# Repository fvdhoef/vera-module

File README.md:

# VERA module - Video Embedded Retro Adapter
This repository contains the files related to the VERA module. This module is developed for the Commander X16 computer by The 8-Bit Guy.

**NOTE**: The Commander X16 logo is part of the Commander X16 project and should not be used when the module is used with other projects.

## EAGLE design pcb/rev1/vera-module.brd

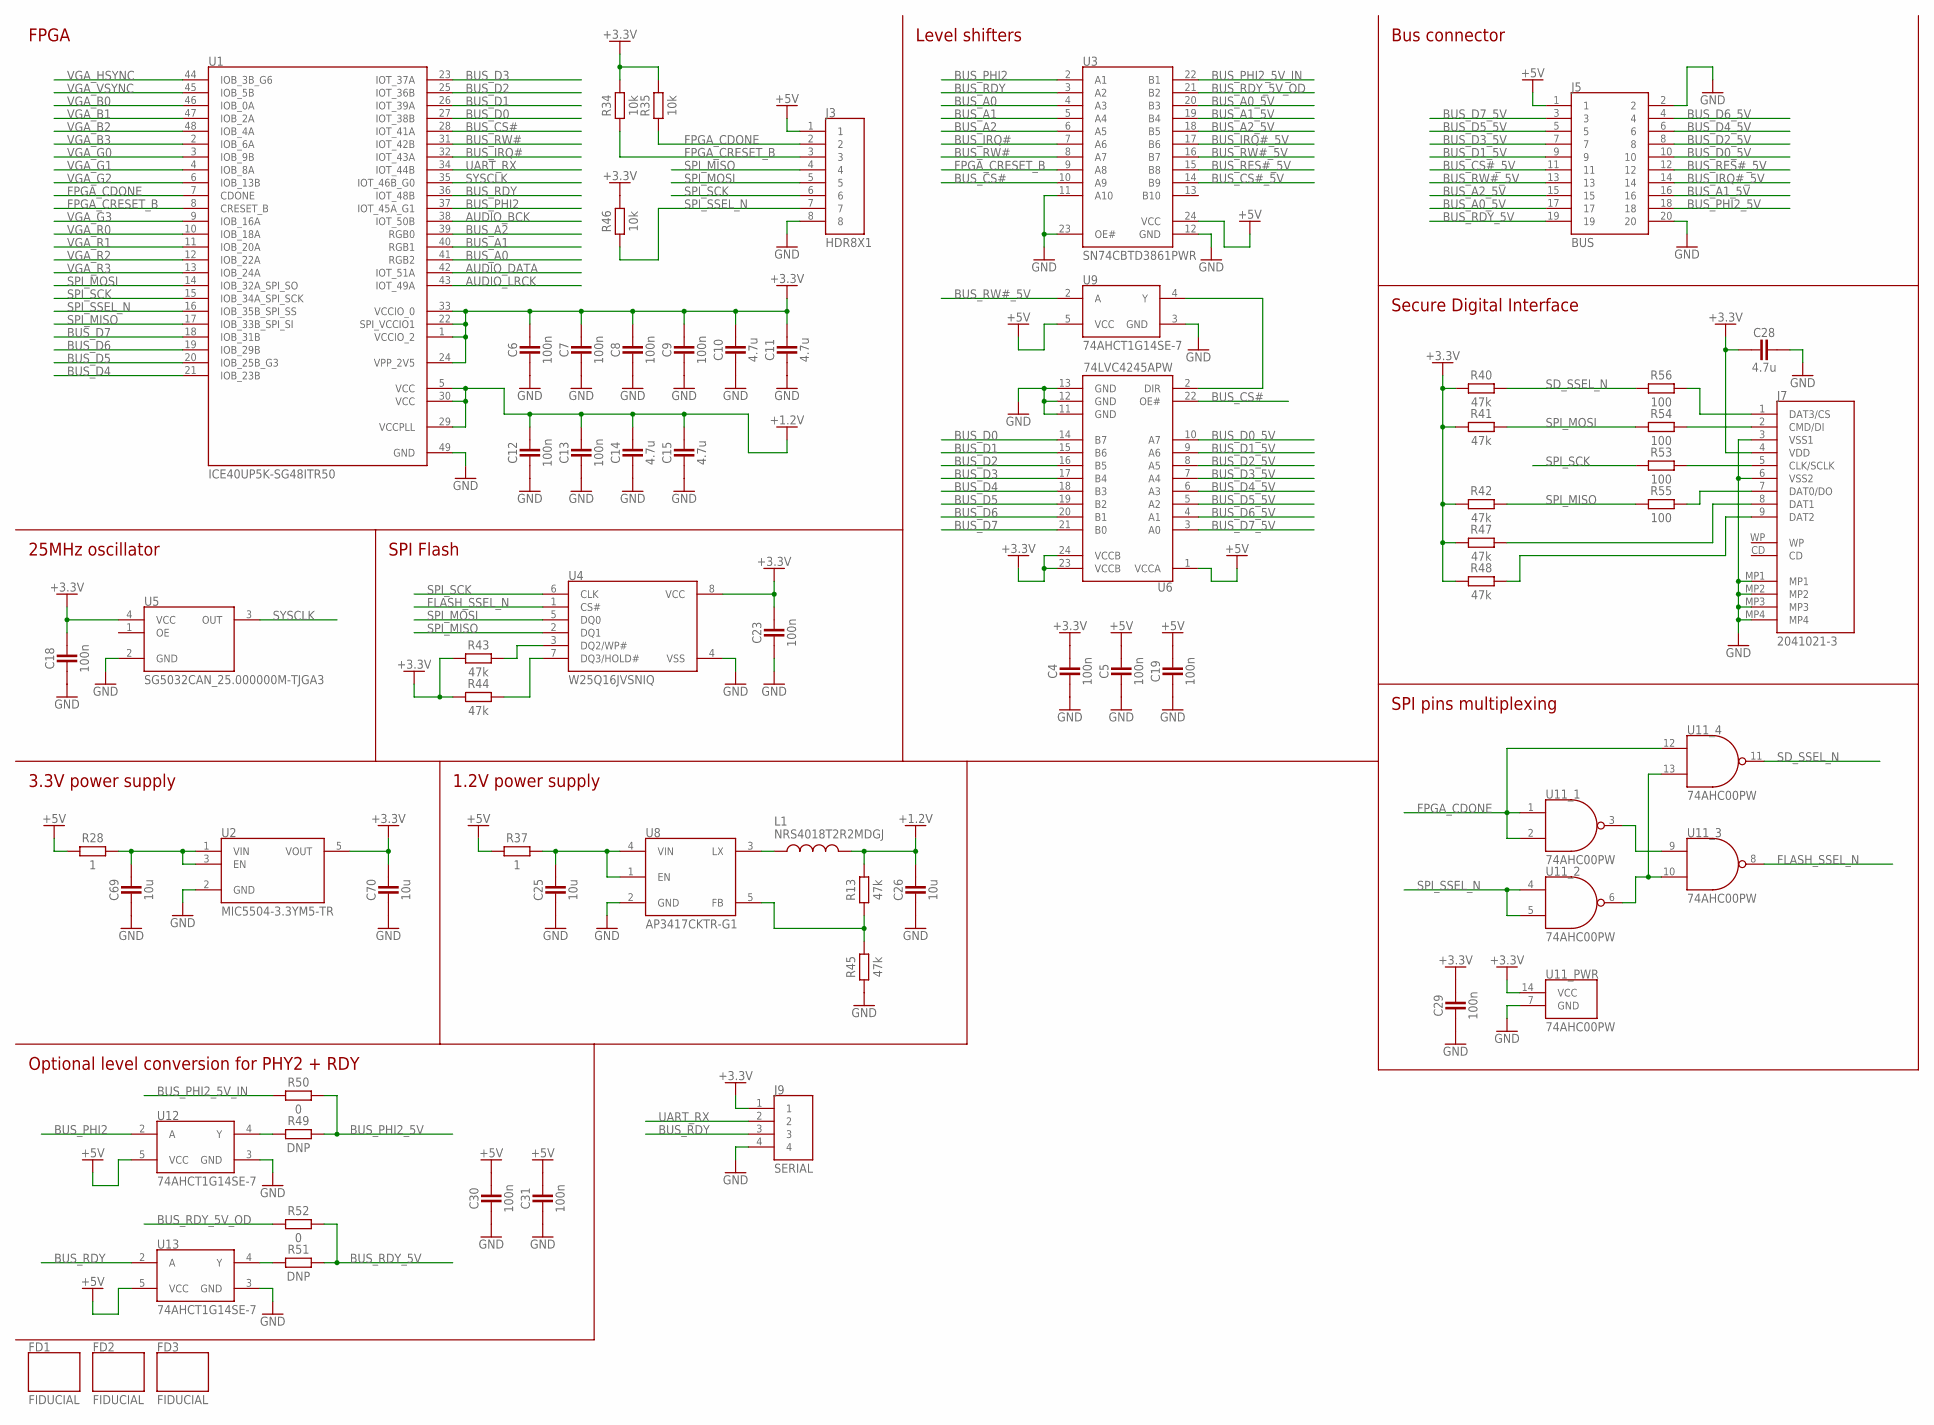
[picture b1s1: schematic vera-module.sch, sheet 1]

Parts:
C4, C5, C6, C7, C8, C9, C12, C13, C18, C19, C23, C29, C30, C31: 100n; C0603
C10, C11, C14, C15, C28: 4.7u; C0603
C25, C26, C69, C70: 10u; C0805
FD1, FD2, FD3: FIDUCIAL
J3: HDR8X1
J5: BUS; HDR2X10
J7: 2041021-3
J9: SERIAL; HDR4X1
L1: NRS4018T2R2MDGJ; NRS4018
R13, R40, R41, R42, R43, R44, R45, R47, R48: 47k; R0603
R28, R37: 1; R0603
R34, R35, R46: 10k; R0603
R49, R51: DNP; R0603
R50, R52: 0; R0603
R53, R54, R55, R56: 100; R0603
U1: ICE40UP5K-SG48ITR50; QFN-48
U2: MIC5504-3.3YM5-TR; SOT-23-5
U3: SN74CBTD3861PWR; TSSOP-24
U4: W25Q16JVSNIQ; SOIC-8
U5: SG5032CAN_25.000000M-TJGA3; SG5032
U6: 74LVC4245APW; TSSOP-24
U8: AP3417CKTR-G1; SOT-23-5
U9, U12, U13: 74AHCT1G14SE-7; TSSOP-5
U11: 74AHC00PW; TSSOP-14

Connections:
+1.2V: C12.2, C13.2, C14.2, C15.2, C26.2, L1.2, R13.2, U1.5 (VCC), U1.29 (VCCPLL), U1.30 (VCC)
+3.3V: C4.2, C6.2, C7.2, C8.2, C9.2, C10.2, C11.2, C18.2, C23.2, C28.1, C29.2, C70.2, J7.4 (VDD), J9.1, R34.1, R35.1, R40.1, R41.1, R42.1, R43.1, R44.1, R46.1, R47.1, R48.1, U1.1 (VCCIO_2), U1.22 (SPI_VCCIO1), U1.24 (VPP_2V5), U1.33 (VCCIO_0), U2.5 (VOUT), U4.8 (VCC), U5.4 (VCC), U6.23 (VCCB), U6.24 (VCCB), U11.14 (VCC); also elsewhere on the board
+5V: C5.2, C19.2, C30.2, C31.2, J3.1, J5.1, R28.1, R37.1, U3.24 (VCC), U6.1 (VCCA), U9.5 (VCC), U12.5 (VCC), U13.5 (VCC)
AUDIO_BCK: U1.38 (IOT_50B); also elsewhere on the board
AUDIO_DATA: U1.42 (IOT_51A); also elsewhere on the board
AUDIO_LRCK: U1.43 (IOT_49A); also elsewhere on the board
BUS_A0: U1.41 (RGB2), U3.4 (A3)
BUS_A0_5V: J5.17, U3.20 (B3)
BUS_A1: U1.40 (RGB1), U3.5 (A4)
BUS_A1_5V: J5.16, U3.19 (B4)
BUS_A2: U1.39 (RGB0), U3.6 (A5)
BUS_A2_5V: J5.15, U3.18 (B5)
BUS_CS#: U1.28 (IOT_41A), U3.10 (A9), U6.22 (OE#)
BUS_CS#_5V: J5.11, U3.14 (B9)
BUS_D0: U1.27 (IOT_38B), U6.14 (B7)
BUS_D0_5V: J5.10, U6.10 (A7)
BUS_D1: U1.26 (IOT_39A), U6.15 (B6)
BUS_D1_5V: J5.9, U6.9 (A6)
BUS_D2: U1.25 (IOT_36B), U6.16 (B5)
BUS_D2_5V: J5.8, U6.8 (A5)
BUS_D3: U1.23 (IOT_37A), U6.17 (B4)
BUS_D3_5V: J5.7, U6.7 (A4)
BUS_D4: U1.21 (IOB_23B), U6.18 (B3)
BUS_D4_5V: J5.6, U6.6 (A3)
BUS_D5: U1.20 (IOB_25B_G3), U6.19 (B2)
BUS_D5_5V: J5.5, U6.5 (A2)
BUS_D6: U1.19 (IOB_29B), U6.20 (B1)
BUS_D6_5V: J5.4, U6.4 (A1)
BUS_D7: U1.18 (IOB_31B), U6.21 (B0)
BUS_D7_5V: J5.3, U6.3 (A0)
BUS_IRQ#: U1.32 (IOT_43A), U3.7 (A6)
BUS_IRQ#_5V: J5.14, U3.17 (B6)
BUS_PHI2: U1.37 (IOT_45A_G1), U3.2 (A1), U12.2 (A)
BUS_PHI2_5V: J5.18, R49.2, R50.2
BUS_PHI2_5V_IN: R50.1, U3.22 (B1)
BUS_RDY: J9.3, U1.36 (IOT_48B), U3.3 (A2), U13.2 (A)
BUS_RDY_5V: J5.19, R51.2, R52.2
BUS_RDY_5V_OD: R52.1, U3.21 (B2)
BUS_RES#_5V: J5.12, U3.15 (B8)
BUS_RW#: U1.31 (IOT_42B), U3.8 (A7)
BUS_RW#_5V: J5.13, U3.16 (B7), U9.2 (A)
FLASH_SSEL_N: U4.1 (CS#), U11.8 (Y)
FPGA_CDONE: J3.2, R35.2, U1.7 (CDONE), U11.1 (A), U11.2 (B), U11.12 (A)
FPGA_CRESET_B: J3.3, R34.2, U1.8 (CRESET_B), U3.9 (A8)
GND: C4.1, C5.1, C6.1, C7.1, C8.1, C9.1, C10.1, C11.1, C12.1, C13.1, C14.1, C15.1, C18.1, C19.1, C23.1, C25.1, C26.1, C28.2, C29.1, C30.1, C31.1, C69.1, C70.1, J3.8, J5.2, J5.20, J7.3 (VSS1), J7.6 (VSS2), J7.MP1, J7.MP2, J7.MP3, J7.MP4, J9.4, R45.1, U1.49 (GND), U2.2 (GND), U3.11 (A10), U3.12 (GND), U3.23 (OE#), U4.4 (VSS), U5.2 (GND), U6.11 (GND), U6.12 (GND), U6.13 (GND), U8.2 (GND), U9.3 (GND), U11.7 (GND), U12.3 (GND), U13.3 (GND); also elsewhere on the board
unnamed: C69.2, R28.2, U2.1 (VIN), U2.3 (EN)
unnamed: U6.2 (DIR), U9.4 (Y)
unnamed: R43.2, U4.3 (DQ2/WP#)
unnamed: R13.1, R45.2, U8.5 (FB)
unnamed: R44.2, U4.7 (DQ3/HOLD#)
unnamed: L1.1, U8.3 (LX)
unnamed: C25.2, R37.2, U8.1 (EN), U8.4 (VIN)
unnamed: J7.8 (DAT1), R47.2
unnamed: J7.9 (DAT2), R48.2
unnamed: U11.3 (Y), U11.9 (A)
unnamed: U11.6 (Y), U11.10 (B), U11.13 (B)
unnamed: R49.1, U12.4 (Y)
unnamed: R51.1, U13.4 (Y)
unnamed: J7.2 (CMD/DI), R54.2
unnamed: J7.5 (CLK/SCLK), R53.2
unnamed: J7.1 (DAT3/CS), R56.2
unnamed: J7.7 (DAT0/DO), R55.2
SD_SSEL_N: R40.2, R56.1, U11.11 (Y)
SPI_MISO: J3.4, R42.2, R55.1, U1.17 (IOB_33B_SPI_SI), U4.2 (DQ1)
SPI_MOSI: J3.5, R41.2, R54.1, U1.14 (IOB_32A_SPI_SO), U4.5 (DQ0)
SPI_SCK: J3.6, R53.1, U1.15 (IOB_34A_SPI_SCK), U4.6 (CLK)
SPI_SSEL_N: J3.7, R46.2, U1.16 (IOB_35B_SPI_SS), U11.4 (A), U11.5 (B)
SYSCLK: U1.35 (IOT_46B_G0), U5.3 (OUT); also elsewhere on the board
UART_RX: J9.2, U1.34 (IOT_44B)
VGA_B0: U1.46 (IOB_0A); also elsewhere on the board
VGA_B1: U1.47 (IOB_2A); also elsewhere on the board
VGA_B2: U1.48 (IOB_4A); also elsewhere on the board
VGA_B3: U1.2 (IOB_6A); also elsewhere on the board
VGA_G0: U1.3 (IOB_9B); also elsewhere on the board
VGA_G1: U1.4 (IOB_8A); also elsewhere on the board
VGA_G2: U1.6 (IOB_13B); also elsewhere on the board
VGA_G3: U1.9 (IOB_16A); also elsewhere on the board
VGA_HSYNC: U1.44 (IOB_3B_G6); also elsewhere on the board
VGA_R0: U1.10 (IOB_18A); also elsewhere on the board
VGA_R1: U1.11 (IOB_20A); also elsewhere on the board
VGA_R2: U1.12 (IOB_22A); also elsewhere on the board
VGA_R3: U1.13 (IOB_24A); also elsewhere on the board
VGA_VSYNC: U1.45 (IOB_5B); also elsewhere on the board

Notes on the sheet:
FPGA
3.3V power supply
25MHz oscillator
SPI Flash
1.2V power supply
Level shifters
Bus connector
Secure Digital Interface
SPI pins multiplexing
Optional level conversion for PHY2 + RDY

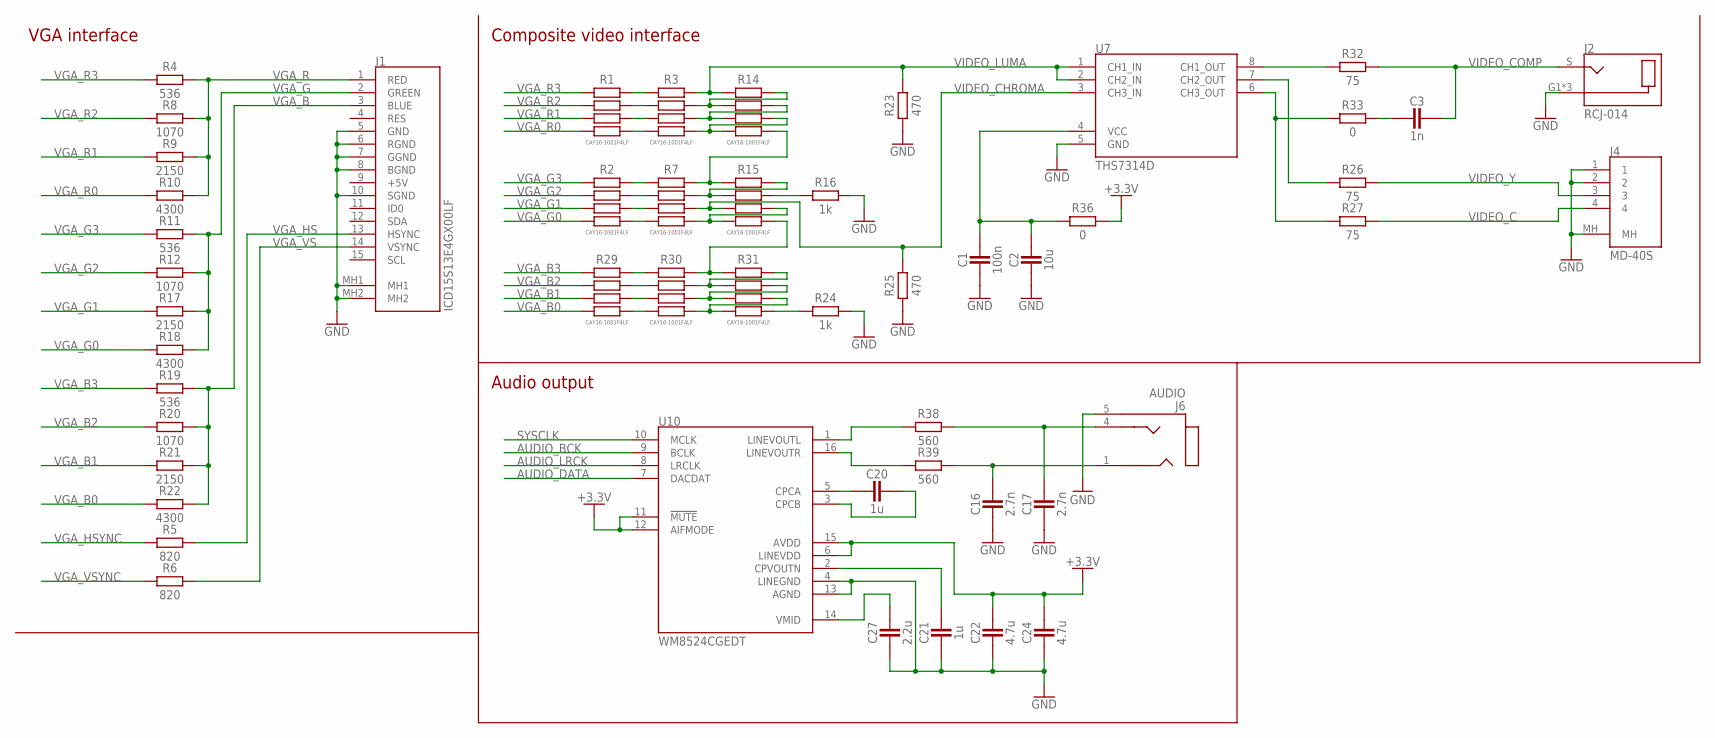
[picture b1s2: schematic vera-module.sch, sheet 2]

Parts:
C1: 100n; C0603
C2: 10u; C0805
C3: 1n; C0603
C16, C17: 2.7n; C0603
C20, C21: 1u; C0603
C22, C24: 4.7u; C0603
C27: 2.2u; C0603
J1: ICD15S13E4GX00LF; 1-1734344-2
J2: RCJ-014; RCJ-01X
J4: MD-40S
J6: AUDIO; 35RASMT2BHNTRX
R1, R2, R3, R7, R14, R15, R29, R30, R31: CAY16-1001F4LF; RA4_1206
R4, R11, R19: 536; R0603
R5, R6: 820; R0603
R8, R12, R20: 1070; R0603
R9, R17, R21: 2150; R0603
R10, R18, R22: 4300; R0603
R16, R24: 1k; R0603
R23, R25: 470; R0603
R26, R27, R32: 75; R0603
R33, R36: 0; R0603
R38, R39: 560; R0603
U7: THS7314D; SOIC-8
U10: WM8524CGEDT; TSSOP-16

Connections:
+3.3V: C22.2, C24.2, R36.2, U10.6 (LINEVDD), U10.11 (!MUTE), U10.12 (AIFMODE), U10.15 (AVDD); also elsewhere on the board
AUDIO_BCK: U10.9 (BCLK); also elsewhere on the board
AUDIO_DATA: U10.7 (DACDAT); also elsewhere on the board
AUDIO_LRCK: U10.8 (LRCLK); also elsewhere on the board
GND: C1.1, C2.1, C16.1, C17.1, C21.1, C22.1, C24.1, C27.1, J1.5 (GND), J1.6 (RGND), J1.7 (GGND), J1.8 (BGND), J1.10 (SGND), J1.MH1, J1.MH2, J2.G1 (G), J2.G2 (G), J2.G3 (G), J4.1, J4.2, J4.MH, J6.5 (SLEEVE), R16.2, R23.1, R24.2, R25.1, U7.5 (GND), U10.4 (LINEGND), U10.13 (AGND); also elsewhere on the board
unnamed: R1.1A, R3.1B
unnamed: R1.2A, R3.2B
unnamed: R1.3A, R3.3B
unnamed: R1.4A, R3.4B
unnamed: R2.1A, R7.1B
unnamed: R2.2A, R7.2B
unnamed: R29.1A, R30.1B
unnamed: R2.3A, R7.3B
unnamed: R2.4A, R7.4B
unnamed: R27.1, R33.1, U7.6 (CH3_OUT)
unnamed: R3.2A, R14.1A, R14.2B
unnamed: R3.3A, R14.2A, R14.3B
unnamed: R3.4A, R14.3A, R14.4B
unnamed: R7.1A, R14.4A, R15.1B
unnamed: R7.2A, R15.1A, R15.2B
unnamed: R32.1, U7.8 (CH1_OUT)
unnamed: C3.1, R33.2
unnamed: R7.4A, R15.3A, R15.4B
unnamed: C20.2, U10.3 (CPCB)
unnamed: R29.2A, R30.2B
unnamed: R29.3A, R30.3B
unnamed: R15.2A, R16.1
unnamed: R29.4A, R30.4B
unnamed: R15.4A, R30.1A, R31.1B
unnamed: R30.2A, R31.1A, R31.2B
unnamed: R30.3A, R31.2A, R31.3B
unnamed: R24.1, R31.4A
unnamed: R30.4A, R31.3A, R31.4B
unnamed: R26.1, U7.7 (CH2_OUT)
unnamed: C1.2, C2.2, R36.1, U7.4 (VCC)
unnamed: C17.2, J6.4 (TIP), R38.2
unnamed: C16.2, J6.1 (RING), R39.2
unnamed: R38.1, U10.1 (LINEVOUTL)
unnamed: R39.1, U10.16 (LINEVOUTR)
unnamed: C20.1, U10.5 (CPCA)
unnamed: C21.2, U10.2 (CPVOUTN)
unnamed: C27.2, U10.14 (VMID)
SYSCLK: U10.10 (MCLK); also elsewhere on the board
VGA_B: J1.3 (BLUE), R19.2, R20.2, R21.2, R22.2
VGA_B0: R22.1, R29.4B; also elsewhere on the board
VGA_B1: R21.1, R29.3B; also elsewhere on the board
VGA_B2: R20.1, R29.2B; also elsewhere on the board
VGA_B3: R19.1, R29.1B; also elsewhere on the board
VGA_G: J1.2 (GREEN), R11.2, R12.2, R17.2, R18.2
VGA_G0: R2.4B, R18.1; also elsewhere on the board
VGA_G1: R2.3B, R17.1; also elsewhere on the board
VGA_G2: R2.2B, R12.1; also elsewhere on the board
VGA_G3: R2.1B, R11.1; also elsewhere on the board
VGA_HS: J1.13 (HSYNC), R5.2
VGA_HSYNC: R5.1; also elsewhere on the board
VGA_R: J1.1 (RED), R4.2, R8.2, R9.2, R10.2
VGA_R0: R1.4B, R10.1; also elsewhere on the board
VGA_R1: R1.3B, R9.1; also elsewhere on the board
VGA_R2: R1.2B, R8.1; also elsewhere on the board
VGA_R3: R1.1B, R4.1; also elsewhere on the board
VGA_VS: J1.14 (VSYNC), R6.2
VGA_VSYNC: R6.1; also elsewhere on the board
VIDEO_C: J4.4, R27.2
VIDEO_CHROMA: R7.3A, R15.3B, R25.2, U7.3 (CH3_IN)
VIDEO_COMP: C3.2, J2.S, R32.2
VIDEO_LUMA: R3.1A, R14.1B, R23.2, U7.1 (CH1_IN), U7.2 (CH2_IN)
VIDEO_Y: J4.3, R26.2

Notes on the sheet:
VGA interface
Composite video interface
Audio output

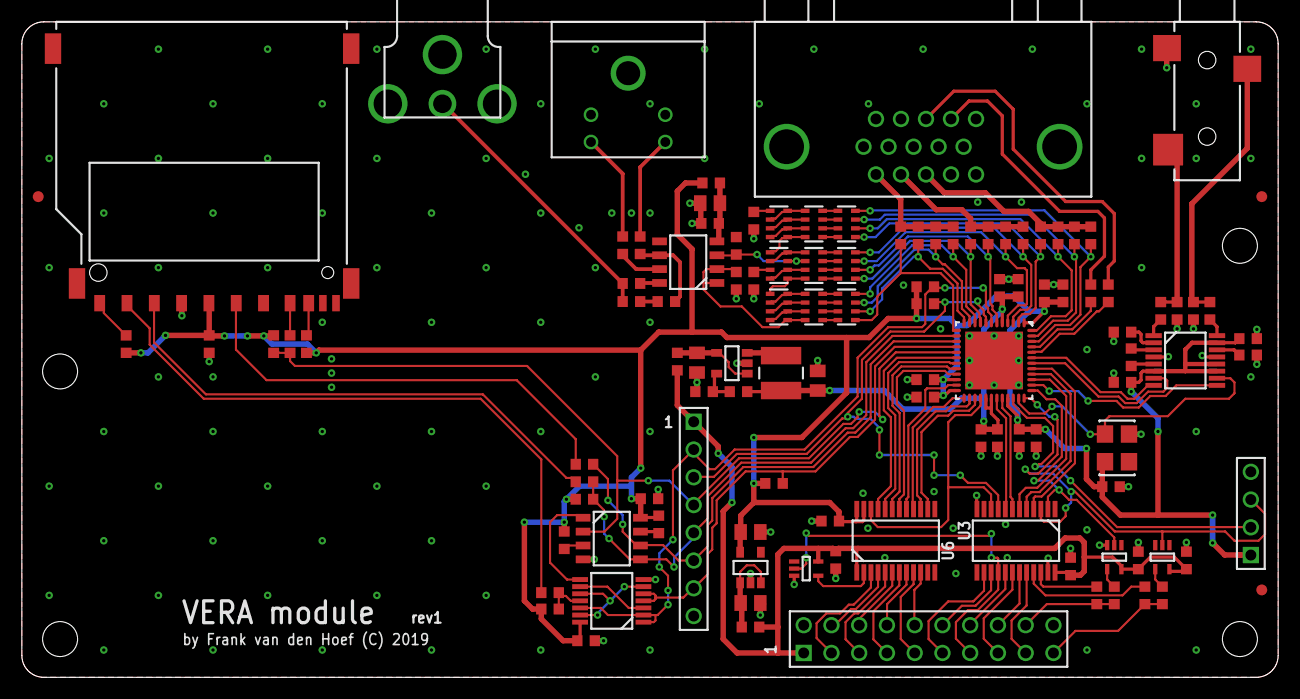
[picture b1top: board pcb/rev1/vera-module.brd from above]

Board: 2 copper layers, 115.0 x 60.0 mm, 114 parts (0 on the bottom side), 130 nets.

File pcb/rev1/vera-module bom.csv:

Qty;Value;Device;Package;Parts
4;0;RESISTOR0603;R0603;R33, R36, R50, R52
2;1;RESISTOR0603;R0603;R28, R37
4;100;RESISTOR0603;R0603;R53, R54, R55, R56
15;100n;CAPACITOR0603;C0603;C1, C4, C5, C6, C7, C8, C9, C12, C13, C18, C19, C23, C29, C30, C31
3;1070;RESISTOR0603;R0603;R8, R12, R20
3;10k;RESISTOR0603;R0603;R34, R35, R46
5;10u;CAPACITOR0805;C0805;C2, C25, C26, C69, C70
2;1k;RESISTOR0603;R0603;R16, R24
1;1n;CAPACITOR0603;C0603;C3
2;1u;CAPACITOR0603;C0603;C20, C21
1;2.2u;CAPACITOR0603;C0603;C27
2;2.7n;CAPACITOR0603;C0603;C16, C17
1;2041021-3;2041021-3;2041021-3;J7
3;2150;RESISTOR0603;R0603;R9, R17, R21
7;4.7u;CAPACITOR0603;C0603;C10, C11, C14, C15, C22, C24, C28
3;4300;RESISTOR0603;R0603;R10, R18, R22
2;470;RESISTOR0603;R0603;R23, R25
9;47k;RESISTOR0603;R0603;R13, R40, R41, R42, R43, R44, R45, R47, R48
3;536;RESISTOR0603;R0603;R4, R11, R19
2;560;RESISTOR0603;R0603;R38, R39
1;74AHC00PW;74AHC00PW;TSSOP-14;U11
3;74AHCT1G14SE-7;74AHCT1G14SE-7;TSSOP-5;U9, U12, U13
1;74LVC4245APW;74LVC4245APW;TSSOP-24;U6
3;75;RESISTOR0603;R0603;R26, R27, R32
2;820;RESISTOR0603;R0603;R5, R6
1;AP3417CKTR-G1;AP3417CKTR-G1;SOT-23-5;U8
1;AUDIO;35RASMT2BHNTRX;35RASMT2BHNTRX;J6
1;BUS;HDR2X10;HDR2X10;J5
9;CAY16-1001F4LF;RES_ARRAY41206;RA4_1206;R1, R2, R3, R7, R14, R15, R29, R30, R31
2;DNP;RESISTOR0603;R0603;R49, R51
3;FIDUCIAL;FIDUCIAL;FIDUCIAL;FD1, FD2, FD3
1;HDR8X1;HDR8X1;HDR8X1;J3
1;ICD15S13E4GX00LF;ICD15S13E4GX00LF;1-1734344-2;J1
1;ICE40UP5K-SG48ITR50;ICE40UP5K-SG48ITR50;QFN-48;U1
1;MD-40S;MD-40S;MD-40S;J4
1;MIC5504-3.3YM5-TR;MIC5504-3.3YM5-TR;SOT-23-5;U2
1;NRS4018T2R2MDGJ;INDUCTORNRS4018;NRS4018;L1
1;RCJ-014;RCJ-014;RCJ-01X;J2
1;SERIAL;HDR4X1;HDR4X1;J9
1;SG5032CAN_25.000000M-TJGA3;SG5032CAN_40.000000M-TJGA3;SG5032;U5
1;SN74CBTD3861PWR;SN74CBTD3861PWR;TSSOP-24;U3
1;THS7314D;THS7314D;SOIC-8;U7
1;W25Q16JVSNIQ;QSPI_FLASHSOIC8;SOIC-8;U4
1;WM8524CGEDT;WM8524CGEDT;TSSOP-16;U10

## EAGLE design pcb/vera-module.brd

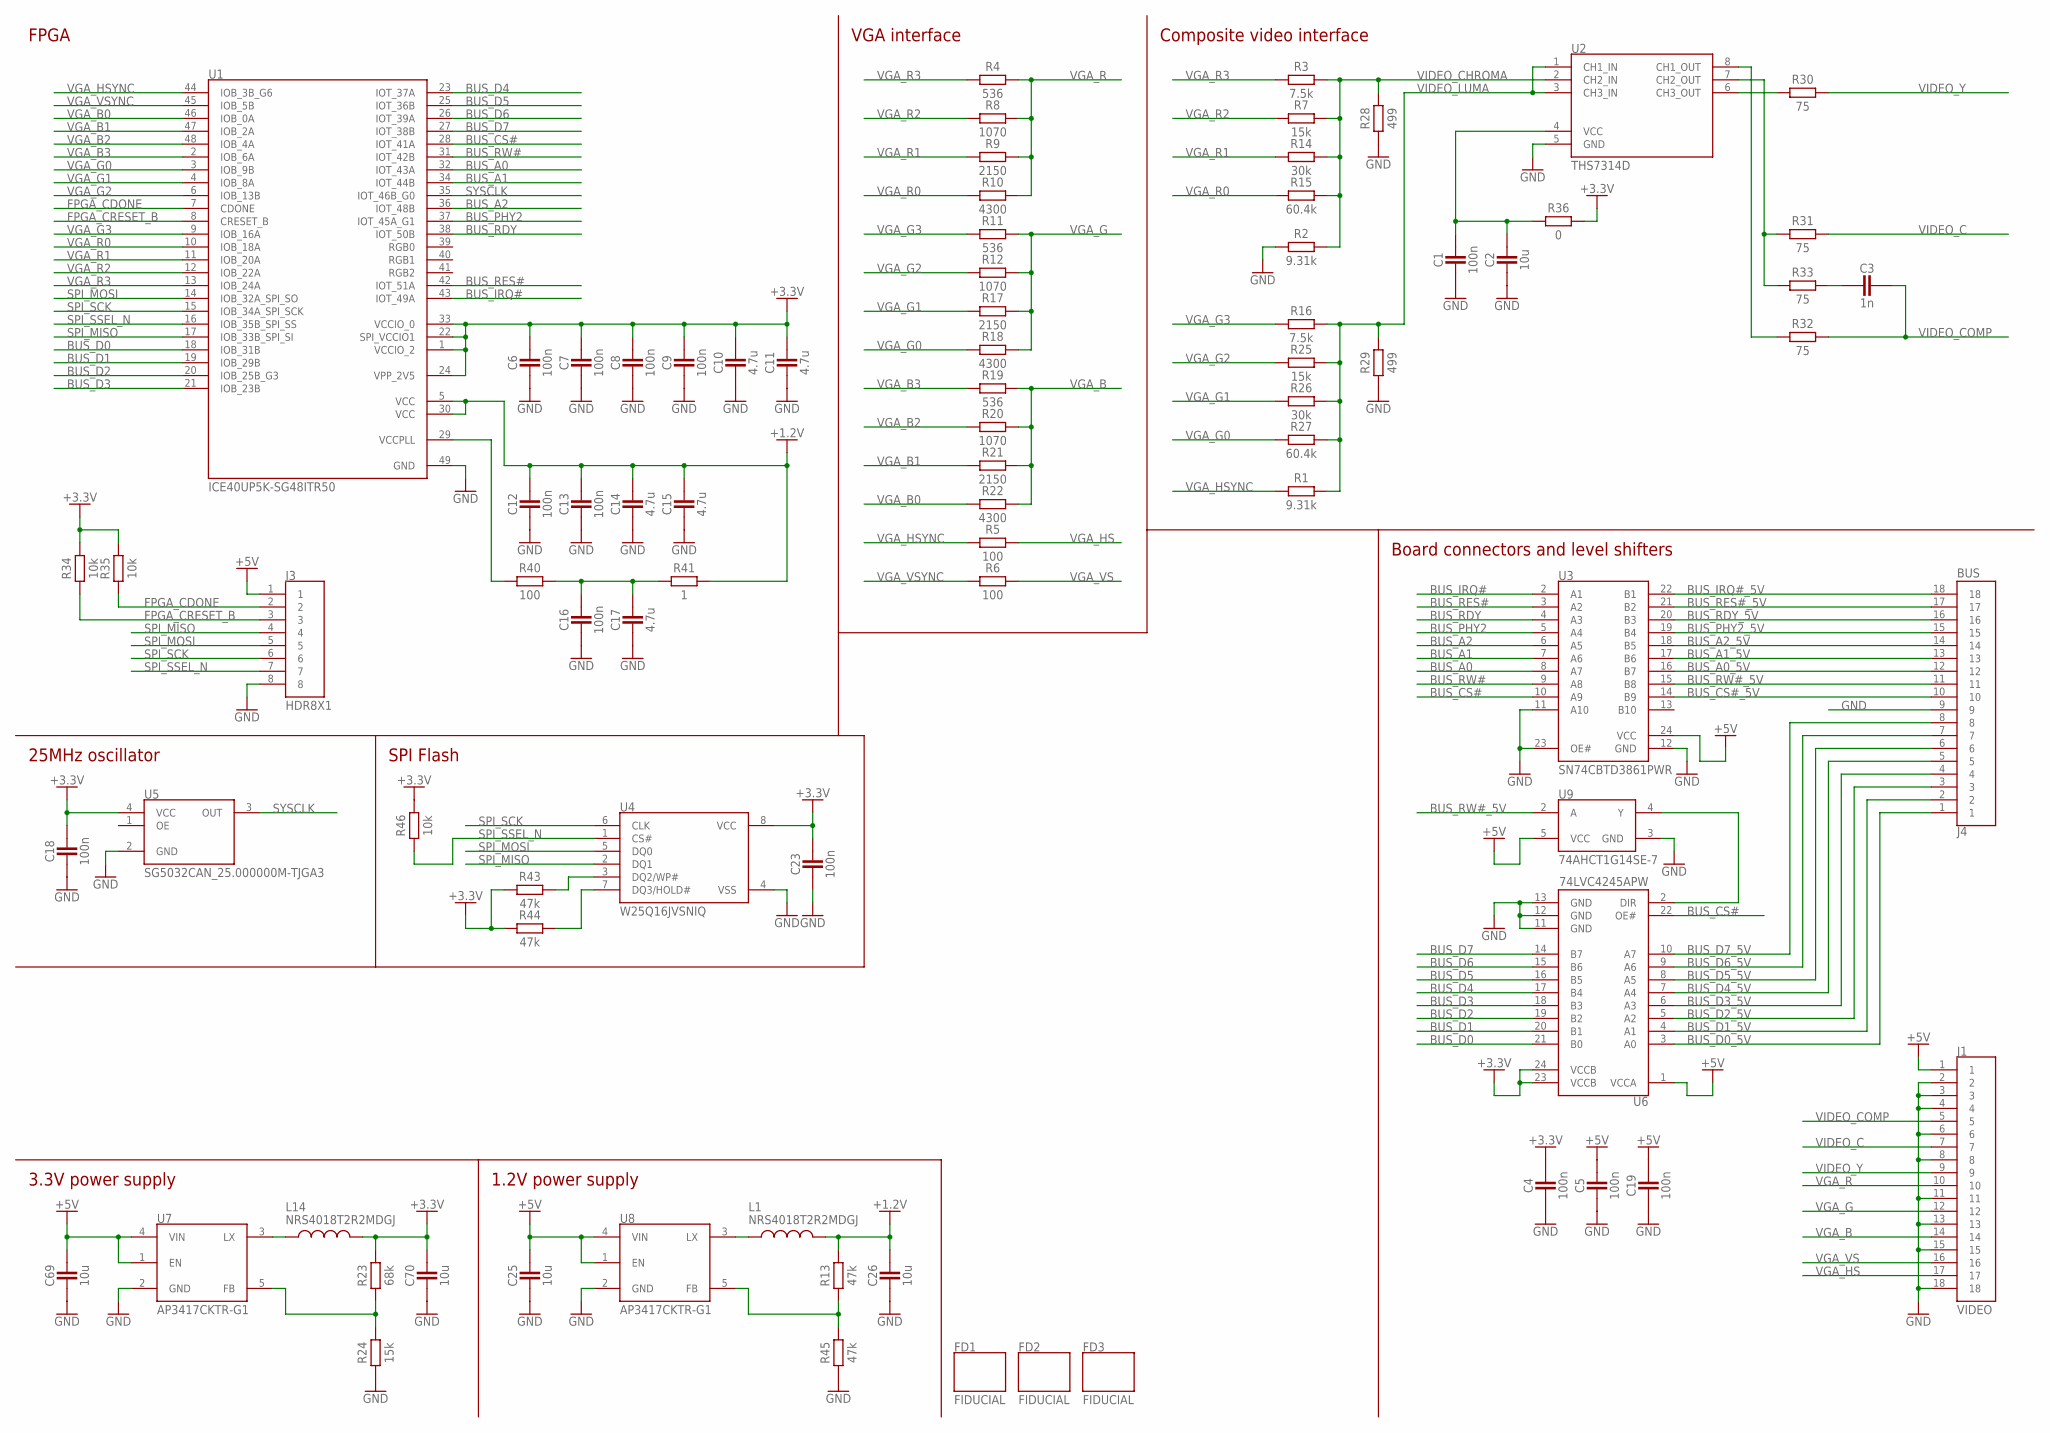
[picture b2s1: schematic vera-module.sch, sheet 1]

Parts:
C1, C4, C5, C6, C7, C8, C9, C12, C13, C16, C18, C19, C23: 100n; C0603
C2, C25, C26, C69, C70: 10u; C0805
C3: 1n; C0603
C10, C11, C14, C15, C17: 4.7u; C0603
FD1, FD2, FD3: FIDUCIAL
J1: VIDEO; HDR18X1
J3: HDR8X1
J4: BUS; HDR18X1
L1, L14: NRS4018T2R2MDGJ; NRS4018
R1, R2: 9.31k; R0603
R3, R16: 7.5k; R0603
R4, R11, R19: 536; R0603
R5, R6, R40: 100; R0603
R7, R24, R25: 15k; R0603
R8, R12, R20: 1070; R0603
R9, R17, R21: 2150; R0603
R10, R18, R22: 4300; R0603
R13, R43, R44, R45: 47k; R0603
R14, R26: 30k; R0603
R15, R27: 60.4k; R0603
R23: 68k; R0603
R28, R29: 499; R0603
R30, R31, R32, R33: 75; R0603
R34, R35, R46: 10k; R0603
R36: 0; R0603
R41: 1; R0603
U1: ICE40UP5K-SG48ITR50; QFN-48
U2: THS7314D; SOIC-8
U3: SN74CBTD3861PWR; TSSOP-24
U4: W25Q16JVSNIQ; SOIC-8
U5: SG5032CAN_25.000000M-TJGA3; SG5032
U6: 74LVC4245APW; TSSOP-24
U7, U8: AP3417CKTR-G1; SOT-23-5
U9: 74AHCT1G14SE-7; TSSOP-5

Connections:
+1.2V: C12.2, C13.2, C14.2, C15.2, C26.2, L1.2, R13.2, R41.2, U1.5 (VCC), U1.30 (VCC)
+3.3V: C4.2, C6.2, C7.2, C8.2, C9.2, C10.2, C11.2, C18.2, C23.2, C70.2, L14.2, R23.2, R34.1, R35.1, R36.2, R43.1, R44.1, R46.1, U1.1 (VCCIO_2), U1.22 (SPI_VCCIO1), U1.24 (VPP_2V5), U1.33 (VCCIO_0), U4.8 (VCC), U5.4 (VCC), U6.23 (VCCB), U6.24 (VCCB)
+5V: C5.2, C19.2, C25.2, C69.2, J1.1, J3.1, U3.24 (VCC), U6.1 (VCCA), U7.1 (EN), U7.4 (VIN), U8.1 (EN), U8.4 (VIN), U9.5 (VCC); also elsewhere on the board
BUS_A0: U1.32 (IOT_43A), U3.8 (A7)
BUS_A0_5V: J4.12, U3.16 (B7)
BUS_A1: U1.34 (IOT_44B), U3.7 (A6)
BUS_A1_5V: J4.13, U3.17 (B6)
BUS_A2: U1.36 (IOT_48B), U3.6 (A5)
BUS_A2_5V: J4.14, U3.18 (B5)
BUS_CS#: U1.28 (IOT_41A), U3.10 (A9), U6.22 (OE#)
BUS_CS#_5V: J4.10, U3.14 (B9)
BUS_D0: U1.18 (IOB_31B), U6.21 (B0)
BUS_D0_5V: J4.1, U6.3 (A0)
BUS_D1: U1.19 (IOB_29B), U6.20 (B1)
BUS_D1_5V: J4.2, U6.4 (A1)
BUS_D2: U1.20 (IOB_25B_G3), U6.19 (B2)
BUS_D2_5V: J4.3, U6.5 (A2)
BUS_D3: U1.21 (IOB_23B), U6.18 (B3)
BUS_D3_5V: J4.4, U6.6 (A3)
BUS_D4: U1.23 (IOT_37A), U6.17 (B4)
BUS_D4_5V: J4.5, U6.7 (A4)
BUS_D5: U1.25 (IOT_36B), U6.16 (B5)
BUS_D5_5V: J4.6, U6.8 (A5)
BUS_D6: U1.26 (IOT_39A), U6.15 (B6)
BUS_D6_5V: J4.7, U6.9 (A6)
BUS_D7: U1.27 (IOT_38B), U6.14 (B7)
BUS_D7_5V: J4.8, U6.10 (A7)
BUS_IRQ#: U1.43 (IOT_49A), U3.2 (A1)
BUS_IRQ#_5V: J4.18, U3.22 (B1)
BUS_PHY2: U1.37 (IOT_45A_G1), U3.5 (A4)
BUS_PHY2_5V: J4.15, U3.19 (B4)
BUS_RDY: U1.38 (IOT_50B), U3.4 (A3)
BUS_RDY_5V: J4.16, U3.20 (B3)
BUS_RES#: U1.42 (IOT_51A), U3.3 (A2)
BUS_RES#_5V: J4.17, U3.21 (B2)
BUS_RW#: U1.31 (IOT_42B), U3.9 (A8)
BUS_RW#_5V: J4.11, U3.15 (B8), U9.2 (A)
FPGA_CDONE: J3.2, R35.2, U1.7 (CDONE); also elsewhere on the board
FPGA_CRESET_B: J3.3, R34.2, U1.8 (CRESET_B); also elsewhere on the board
GND: C1.1, C2.1, C4.1, C5.1, C6.1, C7.1, C8.1, C9.1, C10.1, C11.1, C12.1, C13.1, C14.1, C15.1, C16.1, C17.1, C18.1, C19.1, C23.1, C25.1, C26.1, C69.1, C70.1, J1.2, J1.3, J1.4, J1.6, J1.8, J1.11, J1.13, J1.15, J1.18, J3.8, J4.9, R2.1, R24.1, R28.2, R29.2, R45.1, U1.49 (GND), U2.5 (GND), U3.11 (A10), U3.12 (GND), U3.23 (OE#), U4.4 (VSS), U5.2 (GND), U6.11 (GND), U6.12 (GND), U6.13 (GND), U7.2 (GND), U8.2 (GND), U9.3 (GND); also elsewhere on the board
unnamed: R30.1, U2.6 (CH3_OUT)
unnamed: R31.1, R33.1, U2.7 (CH2_OUT)
unnamed: R32.1, U2.8 (CH1_OUT)
unnamed: C3.1, R33.2
unnamed: R23.1, R24.2, U7.5 (FB)
unnamed: U6.2 (DIR), U9.4 (Y)
unnamed: C16.2, C17.2, R40.2, R41.1
unnamed: R43.2, U4.3 (DQ2/WP#)
unnamed: R13.1, R45.2, U8.5 (FB)
unnamed: R44.2, U4.7 (DQ3/HOLD#)
unnamed: L1.1, U8.3 (LX)
unnamed: L14.1, U7.3 (LX)
unnamed: C1.2, C2.2, R36.1, U2.4 (VCC)
unnamed: R40.1, U1.29 (VCCPLL)
SPI_MISO: J3.4, U1.17 (IOB_33B_SPI_SI), U4.2 (DQ1); also elsewhere on the board
SPI_MOSI: J3.5, U1.14 (IOB_32A_SPI_SO), U4.5 (DQ0); also elsewhere on the board
SPI_SCK: J3.6, U1.15 (IOB_34A_SPI_SCK), U4.6 (CLK); also elsewhere on the board
SPI_SSEL_N: J3.7, R46.2, U1.16 (IOB_35B_SPI_SS), U4.1 (CS#); also elsewhere on the board
SYSCLK: U1.35 (IOT_46B_G0), U5.3 (OUT)
VGA_B: J1.14, R19.2, R20.2, R21.2, R22.2
VGA_B0: R22.1, U1.46 (IOB_0A)
VGA_B1: R21.1, U1.47 (IOB_2A)
VGA_B2: R20.1, U1.48 (IOB_4A)
VGA_B3: R19.1, U1.2 (IOB_6A)
VGA_G: J1.12, R11.2, R12.2, R17.2, R18.2
VGA_G0: R18.1, R27.1, U1.3 (IOB_9B)
VGA_G1: R17.1, R26.1, U1.4 (IOB_8A)
VGA_G2: R12.1, R25.1, U1.6 (IOB_13B)
VGA_G3: R11.1, R16.1, U1.9 (IOB_16A)
VGA_HS: J1.17, R5.2
VGA_HSYNC: R1.1, R5.1, U1.44 (IOB_3B_G6)
VGA_R: J1.10, R4.2, R8.2, R9.2, R10.2
VGA_R0: R10.1, R15.1, U1.10 (IOB_18A)
VGA_R1: R9.1, R14.1, U1.11 (IOB_20A)
VGA_R2: R7.1, R8.1, U1.12 (IOB_22A)
VGA_R3: R3.1, R4.1, U1.13 (IOB_24A)
VGA_VS: J1.16, R6.2
VGA_VSYNC: R6.1, U1.45 (IOB_5B)
VIDEO_C: J1.7, R31.2
VIDEO_CHROMA: R2.2, R3.2, R7.2, R14.2, R15.2, R28.1, U2.2 (CH2_IN)
VIDEO_COMP: C3.2, J1.5, R32.2
VIDEO_LUMA: R1.2, R16.2, R25.2, R26.2, R27.2, R29.1, U2.1 (CH1_IN), U2.3 (CH3_IN)
VIDEO_Y: J1.9, R30.2

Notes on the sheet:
VGA interface
FPGA
3.3V power supply
25MHz oscillator
SPI Flash
1.2V power supply
Composite video interface
Board connectors and level shifters

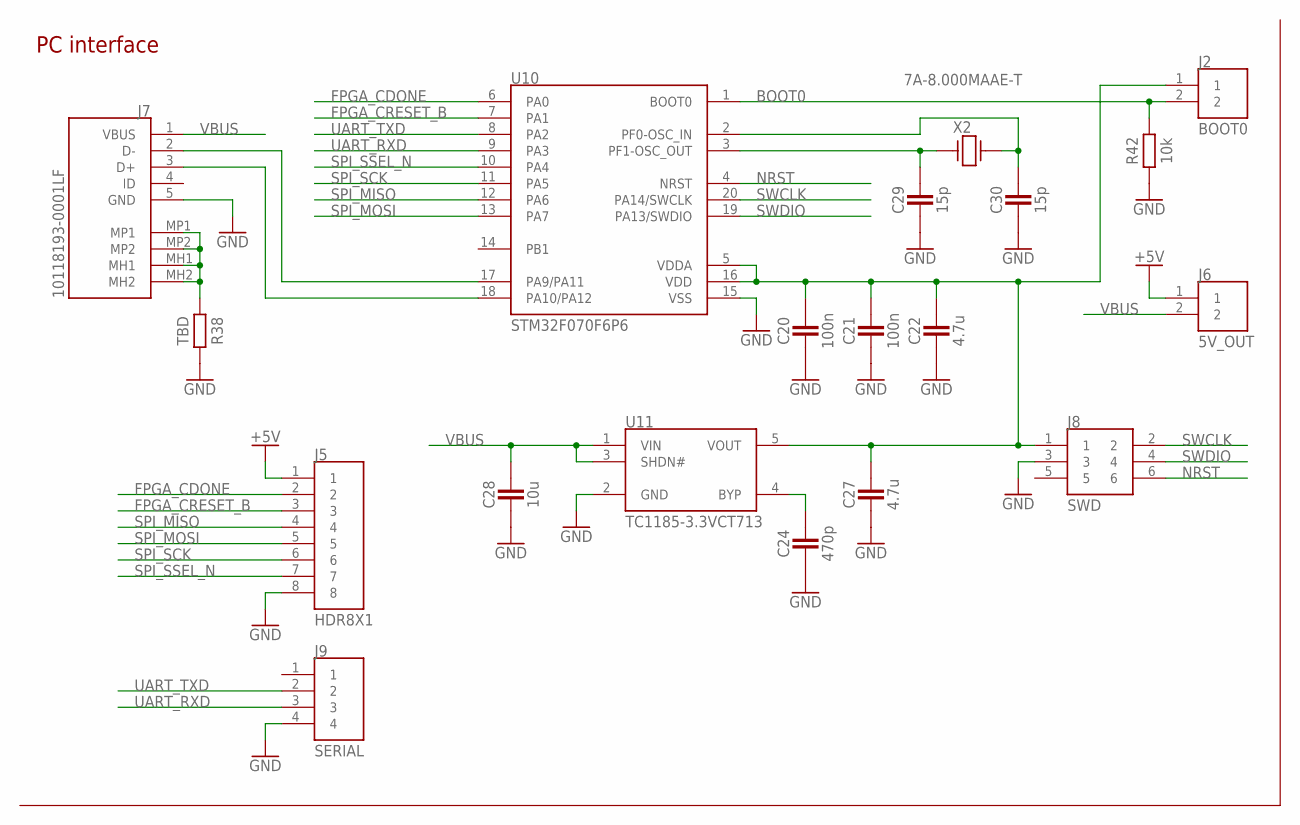
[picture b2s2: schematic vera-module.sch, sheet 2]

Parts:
C20, C21: 100n; C0603
C22, C27: 4.7u; C0603
C24: 470p; C0603
C28: 10u; C0805
C29, C30: 15p; C0603
J2: BOOT0; HDR2X1
J5: HDR8X1
J6: 5V_OUT; HDR2X1
J7: 10118193-0001LF
J8: SWD; HDR2X3
J9: SERIAL; HDR4X1
R38: TBD; R0603
R42: 10k; R0603
U10: STM32F070F6P6; TSSOP-20
U11: TC1185-3.3VCT713; SOT-23-5
X2: 7A-8.000MAAE-T; XTAL2_5X3.2

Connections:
+5V: J5.1, J6.1; also elsewhere on the board
BOOT0: J2.2, R42.2, U10.1 (BOOT0)
FPGA_CDONE: J5.2, U10.6 (PA0); also elsewhere on the board
FPGA_CRESET_B: J5.3, U10.7 (PA1); also elsewhere on the board
GND: C20.1, C21.1, C22.1, C24.1, C27.1, C28.1, C29.1, C30.1, J5.8, J7.5 (GND), J8.3, J9.4, R38.1, R42.1, U10.15 (VSS), U11.2 (GND); also elsewhere on the board
unnamed: C29.2, U10.3 (PF1-OSC_OUT), X2.1
unnamed: C20.2, C21.2, C22.2, C27.2, J2.1, J8.1, U10.5 (VDDA), U10.16 (VDD), U11.5 (VOUT)
unnamed: C24.2, U11.4 (BYP)
unnamed: C30.2, U10.2 (PF0-OSC_IN), X2.2
unnamed: J7.2 (D-), U10.17 (PA9/PA11)
unnamed: J7.3 (D+), U10.18 (PA10/PA12)
unnamed: J7.MH1, J7.MH2, J7.MP1, J7.MP2, R38.2
NRST: J8.6, U10.4 (NRST)
SPI_MISO: J5.4, U10.12 (PA6); also elsewhere on the board
SPI_MOSI: J5.5, U10.13 (PA7); also elsewhere on the board
SPI_SCK: J5.6, U10.11 (PA5); also elsewhere on the board
SPI_SSEL_N: J5.7, U10.10 (PA4); also elsewhere on the board
SWCLK: J8.2, U10.20 (PA14/SWCLK)
SWDIO: J8.4, U10.19 (PA13/SWDIO)
UART_RXD: J9.3, U10.9 (PA3)
UART_TXD: J9.2, U10.8 (PA2)
VBUS: C28.2, J6.2, J7.1 (VBUS), U11.1 (VIN), U11.3 (SHDN#)

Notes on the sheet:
PC interface

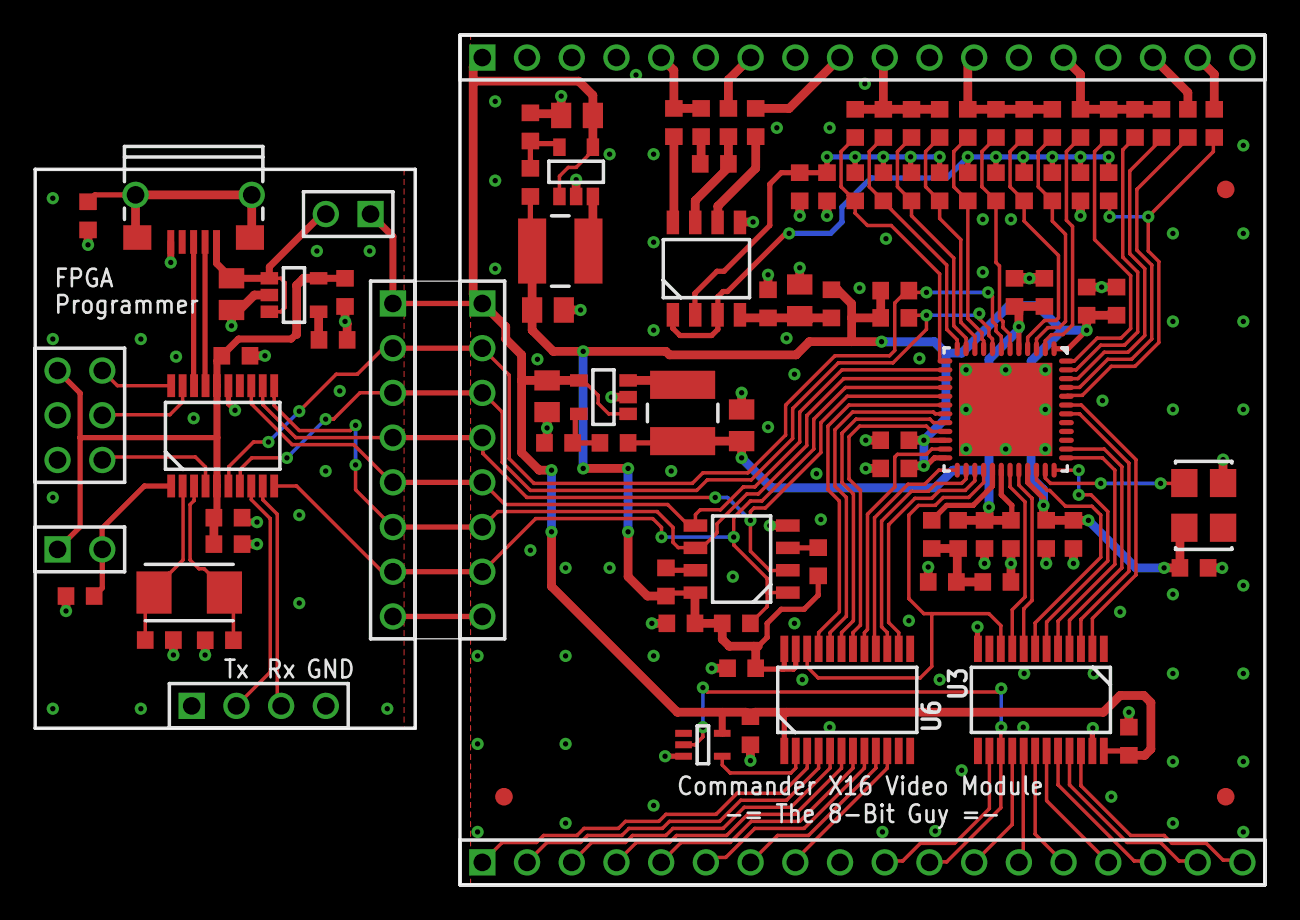
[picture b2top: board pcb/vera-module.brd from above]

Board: 2 copper layers, 69.8 x 48.3 mm, 102 parts (0 on the bottom side), 97 nets.

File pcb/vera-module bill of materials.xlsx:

Qty | Value | Device | Package | Parts | Description
15 | 100n | CAPACITOR0603 | C0603 | C1, C4, C5, C6, C7, C8, C9, C12, C13, C16, C18, C19, C20, C21, C23
7 | 4.7u | CAPACITOR0603 | C0603 | C10, C11, C14, C15, C17, C22, C27
6 | 10u | CAPACITOR0805 | C0805 | C2, C25, C26, C28, C69, C70
1 | 470p | CAPACITOR0603 | C0603 | C24
2 | 15p | CAPACITOR0603 | C0603 | C29, C30
1 | 1n | CAPACITOR0603 | C0603 | C3
3 | FIDUCIAL | FIDUCIAL | FIDUCIAL | FD1, FD2, FD3
1 | VIDEO | HDR18X1 | HDR18X1 | J1
1 | BOOT0 | HDR2X1 | HDR2X1 | J2
2 | HDR8X1 | HDR8X1 | HDR8X1 | J3, J5
1 | BUS | HDR18X1 | HDR18X1 | J4
1 | 5V_OUT | HDR2X1 | HDR2X1 | J6
1 | 10118193-0001LF | 10118193-0001LF | 10118193-0001LF | J7
1 | SWD | HDR2X3 | HDR2X3 | J8
1 | SERIAL | HDR4X1 | HDR4X1 | J9
2 | NRS4018T2R2MDGJ | INDUCTORNRS4018 | NRS4018 | L1, L14
2 | 9.31k | RESISTOR0603 | R0603 | R1, R2
3 | 4300 | RESISTOR0603 | R0603 | R10, R18, R22
4 | 47k | RESISTOR0603 | R0603 | R13, R43, R44, R45
2 | 30k | RESISTOR0603 | R0603 | R14, R26
2 | 60.4k | RESISTOR0603 | R0603 | R15, R27
1 | 68k | RESISTOR0603 | R0603 | R23
2 | 499 | RESISTOR0603 | R0603 | R28, R29
2 | 7.5k | RESISTOR0603 | R0603 | R3, R16
4 | 75 | RESISTOR0603 | R0603 | R30, R31, R32, R33
4 | 10k | RESISTOR0603 | R0603 | R34, R35, R42, R46
1 | 0 | RESISTOR0603 | R0603 | R36
1 | TBD | RESISTOR0603 | R0603 | R38
3 | 536 | RESISTOR0603 | R0603 | R4, R11, R19
1 | 1 | RESISTOR0603 | R0603 | R41
3 | 100 | RESISTOR0603 | R0603 | R5, R6, R40
3 | 15k | RESISTOR0603 | R0603 | R7, R24, R25
3 | 1070 | RESISTOR0603 | R0603 | R8, R12, R20
3 | 2150 | RESISTOR0603 | R0603 | R9, R17, R21
1 | ICE40UP5K-SG48ITR50 | ICE40UP5K-SG48ITR50 | QFN-48 | U1 | Lattice ICE40 5K LE FPGA
1 | STM32F070F6P6 | STM32F070F6P6 | TSSOP-20 | U10 | ARM Cortex M0 with USB 32KB Flash, 6KB RAM
1 | TC1185-3.3VCT713 | TC1185-3.3VCT713 | SOT-23-5 | U11
1 | THS7314D | THS7314D | SOIC-8 | U2
1 | SN74CBTD3861PWR | SN74CBTD3861PWR | TSSOP-24 | U3
1 | W25Q16JVSNIQ | QSPI_FLASHSOIC8 | SOIC-8 | U4
1 | SG5032CAN_25.000000M-TJGA3 | SG5032CAN_40.000000M-TJGA3 | SG5032 | U5 | Epson 40 MHz 3.3V Oscillator +/- 50ppm
1 | 74LVC4245APW | 74LVC4245APW | TSSOP-24 | U6
2 | AP3417CKTR-G1 | AP3417CKTR-G1 | SOT-23-5 | U7, U8
1 | 74AHCT1G14SE-7 | 74AHCT1G14SE-7 | TSSOP-5 | U9
1 | 7A-8.000MAAE-T | XTAL2_5X3.2 | XTAL2_5X3.2 | X2

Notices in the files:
pcb/rev1/vera-module.brd:
by Frank van den Hoef (C) 2019
